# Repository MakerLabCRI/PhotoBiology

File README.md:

# PhotoBiology
Set of cool tools to do research on the affects of Light on cells

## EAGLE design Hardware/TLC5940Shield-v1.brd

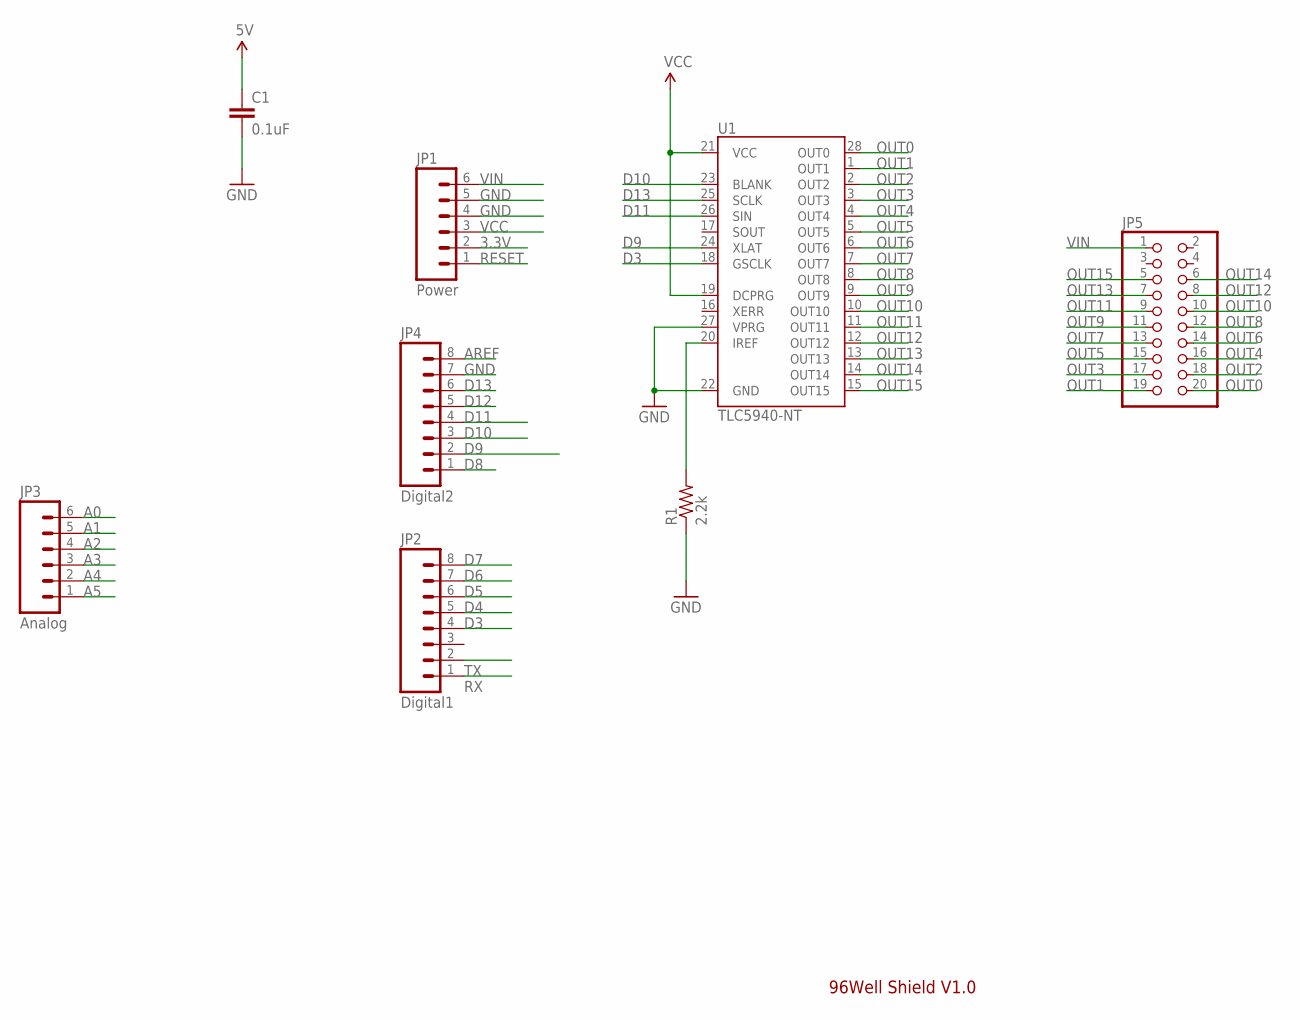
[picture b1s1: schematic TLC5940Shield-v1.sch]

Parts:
C1: 0.1uF; 0402-CAP
JP1: Power; 1X06
JP2: Digital1; 1X08
JP3: Analog; 1X06
JP4: Digital2; 1X08
JP5: PINHD-2X10; 2X10
R1: 2.2k; AXIAL-0.4
U1: TLC5940-NT; DIL28-3

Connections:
3.3V: JP1.2
A0: JP3.6
A1: JP3.5
A2: JP3.4
A3: JP3.3
A4: JP3.2
A5: JP3.1
AREF: JP4.8
D3: JP2.4, U1.18 (GSCLK)
D4: JP2.5
D5: JP2.6
D6: JP2.7
D7: JP2.8
D8: JP4.1
D9: JP4.2, U1.24 (XLAT)
D10: JP4.3, U1.23 (BLANK)
D11: JP4.4, U1.26 (SIN)
D12: JP4.5
D13: JP4.6, U1.25 (SCLK)
GND: C1.2, JP1.4, JP1.5, JP4.7, R1.P$1 (1), U1.22 (GND), U1.27 (VPRG)
unnamed: R1.P$2 (2), U1.20 (IREF)
OUT0: JP5.20, U1.28 (OUT0)
OUT1: JP5.19, U1.1 (OUT1)
OUT2: JP5.18, U1.2 (OUT2)
OUT3: JP5.17, U1.3 (OUT3)
OUT4: JP5.16, U1.4 (OUT4)
OUT5: JP5.15, U1.5 (OUT5)
OUT6: JP5.14, U1.6 (OUT6)
OUT7: JP5.13, U1.7 (OUT7)
OUT8: JP5.12, U1.8 (OUT8)
OUT9: JP5.11, U1.9 (OUT9)
OUT10: JP5.10, U1.10 (OUT10)
OUT11: JP5.9, U1.11 (OUT11)
OUT12: JP5.8, U1.12 (OUT12)
OUT13: JP5.7, U1.13 (OUT13)
OUT14: JP5.6, U1.14 (OUT14)
OUT15: JP5.5, U1.15 (OUT15)
RESET: JP1.1
RX: JP2.1
TX: JP2.2
VCC: C1.1, JP1.3, U1.19 (DCPRG), U1.21 (VCC)
VIN: JP1.6, JP5.1

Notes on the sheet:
96Well Shield V1.0

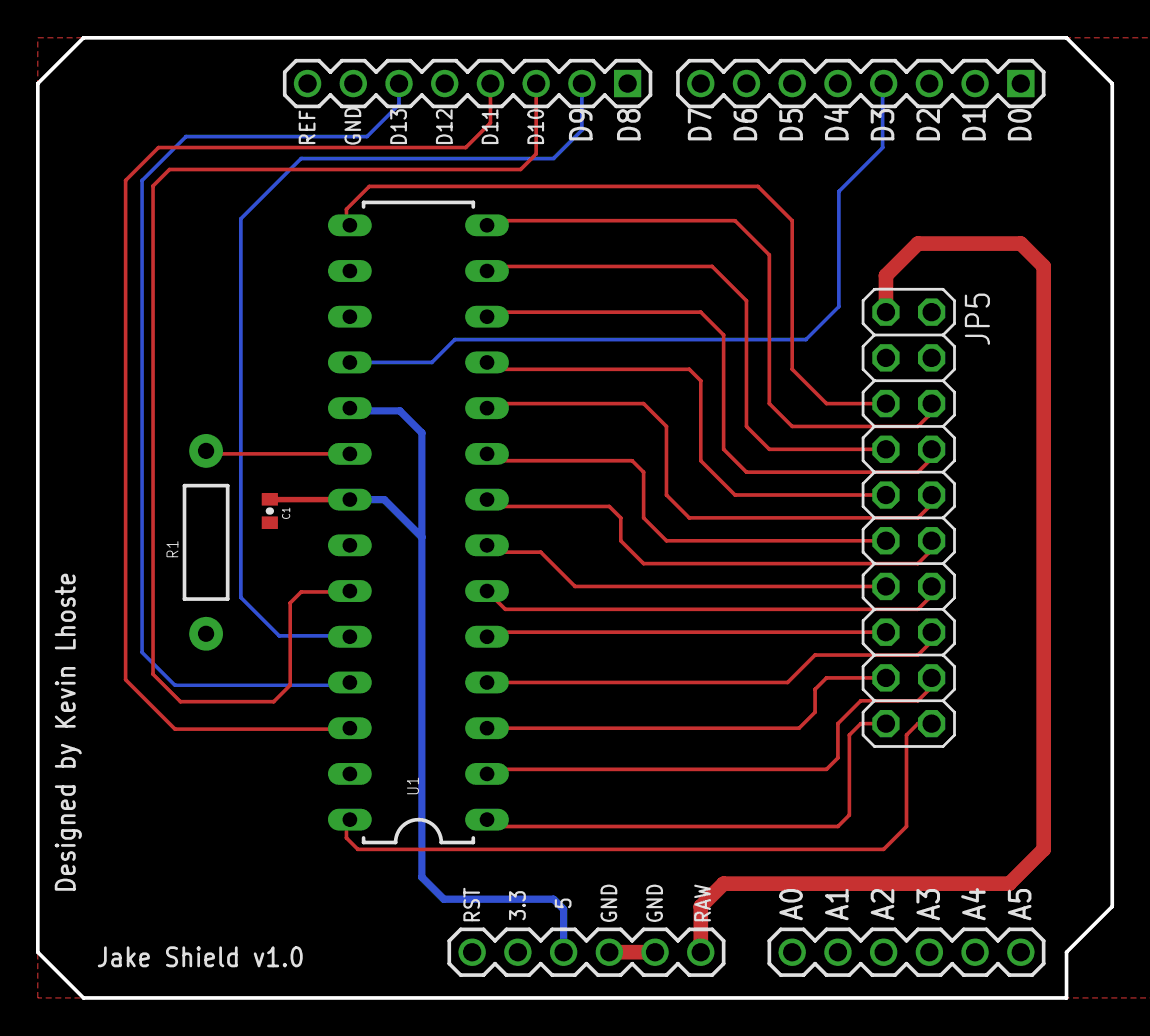
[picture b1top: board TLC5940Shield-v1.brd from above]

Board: 2 copper layers, 59.7 x 53.3 mm, 8 parts (0 on the bottom side), 25 nets.

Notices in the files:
parts and their libraries:
SparkFun-DigitalIC: Licensing: CC v3.0 Share-Alike You are welcome to use this library for commercial purposes.
